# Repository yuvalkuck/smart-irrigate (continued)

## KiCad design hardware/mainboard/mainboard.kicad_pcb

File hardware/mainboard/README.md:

# Mainboard

Schematic: `mainboard.kicad_sch`. The sheet carries only the wire-colour legend. All the notes are here.

## Valve path

* The valve GPIOs come from the board manager file `components/board_manager/board_peripherals.yaml`
  (`gpio_valve_0` to `gpio_valve_7` = GPIO 1, 14, 18, 21, 22, 16, 17, 5), with `CONFIG_DEVICE_MAX_VALVES` = 8.
  All 8 relay channels are valves.
* GPIO 16/17 are UART0, so the console runs on USB Serial/JTAG.
* IO2 and IO3 (header A1, A2) are the only C6 GPIOs on the FireBeetle 2 header that are not connected.
  More valves, the 24 VAC inverter enable (P12), the
  inverter fault input (P15), the mains-detect input (P11) and the charger status inputs (P16 `STAT1`,
  P17 `STAT2`) use the I2C expander U5.
* The 3.3 V valve GPIOs go through two SN74AHCT125N quad buffers: U10 for valves 1-4 and U11 for
  valves 5-8. The buffer outputs go to J15 pins 2-9 (relay inputs IN1..IN8), which get 5 V logic. All
  `/OE` pins are tied to GND, and each chip has a 100 nF decoupling capacitor (C9, C10). The wires from the
  C6 to the buffers are named `VALVE1`-`VALVE8`.
* The 8-channel relay module is off the board. J15 (1x10, 2.54 mm) is its control header: 1 = GND,
  2-9 = IN1-IN8, 10 = +5V.
* The buffer outputs have no pull resistors. The state of the relay inputs while the C6 GPIOs float at
  reset is unknown. It depends on the input circuit of the relay module.
* The relay contacts are on the relay module, not on this board: J2 pin 1 goes to COM1..8, NO1..8 go
  to valves 1..8, and J2 pin 2 goes to the valve common.

## Power

* J1 takes +24 V DC through the 5 A fuse F3. In V1 an external 24 V DC supply feeds J1. When the battery
  add-on (`hardware/battery`) is installed, its J5 (24 V DC out) feeds J1 instead; the mainboard does not change.
* The mainboard makes its own +5V and 24 VAC from +24V. The 5S pack, its gauge and protector (BQ40Z80),
  the charger and the 24 V bus converter are on the battery add-on only.
* Optional addon: one 3.7 V 18650 cell (BT3) plugs into the on-board JST PH2.0 battery socket (J3) of A1, the
  FireBeetle 2 module. The cell and the socket are not on this board's schematic or PCB. The FireBeetle 2
  on-board charger charges the cell.
* J16 (1x8 pin header, 2.54 mm) is the link to the battery add-on J4: 1 = +5V (out, if the add-on needs it), 2 = GND,
  3 = +3V3 (out), 4 = SDA, 5 = SCL, 6 = `MAINS_OK_N` (in), 7 = `STAT1` (in), 8 = `STAT2` (in).
  `MAINS_OK_N`, `STAT1` and `STAT2` are open-drain outputs of the add-on charger, so R64, R65 and R66
  (100k to +3V3) pull them up. `MAINS_OK_N` goes to U5 P11, `STAT1` to P16 and `STAT2` to P17.
  `MAINS_OK_N` high = no mains (or no add-on).
* The battery gauge (BQ40Z80, SMBus) is on the battery add-on and is reached through J16 SDA and SCL. It reports
  each cell voltage, pack voltage and current, remaining capacity and state of charge, temperature and
  protection status. Its SMBus speed is 10 to 100 kHz in slave mode, so the shared I2C bus has to run at
  100 kHz or below when the add-on is fitted. Its slave address is not read yet.
* The ESP32-S3 (A3) runs from the switched 5 V line (DevKit 5V0 pin). Q1 (AO3401A P-FET) connects
  +5V to it, and Q2 (BSS138) drives its gate. R34 (100k) holds Q1 off when Q2 is off. The switched 5 V
  line also feeds the LCD (J6) and the HV side of the level shifter U9.
* U5 P13 controls Q2. R35 (100k) pulls it up to +3V3, so the S3 is on by default (also while P13
  floats at boot). Firmware pulls P13 low to power the S3 down.
* The battery-state LED DS12 (with R33, 470 R) is on U5 P07 (`LED_BAT`).
* The buzzer BZ1 is an active 5 V buzzer (it needs a built-in oscillator). Q3 (BSS138) switches it from
  U5 P14, R36 (2.2k) holds the gate low, and D8 (1N4148W) is the flyback diode.
* R36 and R41 are 2.2k because the U5 (TCA9555) ports power up as inputs with an internal pull-up. The
  datasheet gives 100 uA maximum for that pull-up, so the pin stays at 0.22 V or less. That is below the
  BSS138 threshold (0.5 V minimum) and below the TPS7A1601 `EN` off level (0.3 V).

## 5 V (U12, LMR51430)

* Buck from +24V, 3 A part. R37 (100k) and R38 (13.7k) set 4.98 V. L1 6.8 uH. C15 and C16 are 2 x 22 uF
  output, C12 to C14 the input capacitors. `EN` is tied to +24V.

## 24 VAC (sine inverter)

Moved from the battery board (design values unchanged, references renumbered). It runs whenever +24V is present
and firmware enables it.

* `INV_EN` comes from U5 P12. R41 (2.2k) pulls it low, so the inverter is off until firmware drives it high.
  It gates the 12 V LDO (U13 `EN`), the EG8010 `SPWMEN` and the DRV8412 `RESET_AB`. The 45 V boost enables
  itself from the 12 V rail, so it stops too.
* `INV_FAULT_N` is the DRV8412 `FAULT` pin (open collector, low = fault). It goes to U5 P15 with the R63
  (100k) pull-up to +3V3.
* 12 V (U13, TPS7A1601): R39 (1.15M) over R40 (127k) set about 12 V. C17 feed-forward, C18 input, C19 output.
  It feeds the DRV8412 `GVDD`/`VDD` (about 30 mA) and the boost enable divider. About 0.36 W at 24 V in.
* 45 V boost (U14, LM5155): R49 (107k) over R50 (2.43k) set 45.0 V, R47 (73.2k) about 298 kHz. L2 15 uH,
  Q5 switch, D9 PMEG060V100EPD diode, R44 12 m sense, R45 slope. Output C28/C29 (100 uF 63 V polymer) and
  C30 to C32 (4.7 uF 100 V). Compensation R48, C24, C25 are start values. Enable: R51/R52 divide the 12 V
  rail. Bias from +24V through R42 (0R) with C20.
* EG8010 (U15): bipolar mode, 50 Hz, soft start on, 12 MHz crystal Y1 with C33/C34. `SPWMOUT3` (left-high)
  goes to `PWM_A` through R53/R54, `SPWMOUT1` (right-high) to `PWM_B` through R55/R56 (about 3.5 V from 5 V).
* DRV8412 (U16): mode 000, only bridges A and B used. R62 (36k) sets `OC_ADJ` for about 7.4 A. R61 (1R)
  joins GND and AGND. C39 on `VREG`, C40 to C43 on `GVDD`, C46 to C49 on `PVDD`, C50 to C53 bootstrap.
* Feedback: 47k over 4.53k with 100 nF on each output line (R57/R58/C37, R59/R60/C38) into `VFB` and
  `VFB2`, about 24.1 V RMS. The EG8010 shuts down above 3.15 V peak feedback (300 ms) and below 2.75 V (3 s)
  (EG8010 datasheet, section 8.1).
* Output filter: L3 and L4 (1 mH, one in each line) and C54 (4.7 uF film) across the output. It feeds J2
  through the existing snubber/indicator R6, R30, C3, D7, DS11.

Open points of this block:

* Output common mode: each 24 VAC wire sits at about 22.5 V DC (`PVDD`/2) plus the AC, relative to GND. An
  isolating 50 Hz transformer between C54 and J2 is the proposed fix; not decided and not drawn.
* L3/L4: no part chosen; the footprint is a placeholder. D9: datasheet not read.
* The 45 V boost and the DRV8412 bridge switch near the ESP32 and the sensor inputs: keep them apart on the PCB.

## ESP32-S3 link

* IO6/IO7 are the UART1 link to A3: A3 IO17 TX goes to IO7, and IO6 goes to A3 IO18 RX. J4 (1x3 pin header,
  2.54 mm) is a logic-analyzer tap on the C6 side of the same wires: 1 = `S3_TX`, 2 = `S3_RX`, 3 = GND.
* Q4 (BSS138) isolates the C6 TX line (`S3_RX`, C6 side) from the S3 RX pin (A3 IO18) while the S3 is
  powered down. Its gate is on the switched 5 V line, so the line opens by itself when Q1 cuts the S3 supply. The drain is
  on the C6 side, so the body diode cannot feed the unpowered S3. The S3 TX line (`S3_TX`) needs no
  isolation, and R16 keeps it pulled up on the C6 side.

## RS-485 to the sensor cluster

* J5: 1 = A, 2 = B, 3 = +5V out, 4 = GND.
* The +5V out goes through F2 (MF-RHT050, 0.5 A resettable fuse). D2 (SMAJ5.0A) is on the J5 side of F2,
  and D1 (SM712) is on A and B.
* U4 is on the UART: IO9 TX goes to DI, and IO8 takes RO.
* DE and /RE are on IO15, the on-board LED, which also shows TX. R7 holds DE low at boot.
* R10 (120R) is the terminator, always connected across A and B (no jumper) because this board is the start of
  the bus. R8/R9 are the 390R bias, which sits at this end only.
* SHT41, BMP581 and the solar panel are on the sensor cluster and are read over RS-485 (J5).

## I2C

* The bus is on IO19/IO20 (header pins 28/29; pins 9/10 are the same signals).
* U5 TCA9555 is at 0x20 and U8 ADS1115 is at 0x48 (`ADDR` to GND). R17/R18 are the pull-ups. The bus also
  goes to J16 for the BQ40Z80 gauge on the battery add-on.

## Analog inputs

* U8 (ADS1115) reads all the analog inputs: AIN0 = XDB401 pressure (J9), AIN1 = wind speed (J10),
  AIN2 = board temperature U7 (MCP9700A). AIN3 is free.
* The 1.8k/3.3k dividers (R2/R1 on AIN0, R4/R3 on AIN1) scale the 0-5 V sensor outputs to 0-3.24 V.
* J8 (DS18B20): 1 = +3V3, 2 = GND, 3 = DATA. R5 (4.7k) is the 1-Wire pull-up.
* J9 (XDB401): 1 = +5V, 2 = GND, 3 = OUT.
* J10 (wind sensor): 1 = +24V, 2 = GND, 3 = OUT. The footprint has 4 terminals and terminal 4 has no net.
* Sensor cable TVS: D3 DS18B20, D4 XDB401, D5 wind OUT, D6 wind +24V. R11 limits the IO4 current.

## LCD and keys on the ESP32-S3

* J6 LCD2004 I2C: 1 = GND, 2 = VCC, 3 = SDA, 4 = SCL. On A3: IO8 is SDA and IO9 is SCL. VCC comes from the
  switched 5 V line (Q1 drain), so the LCD is off when the S3 is powered down.
* J7 (1x5 pin header, 2.54 mm) takes the 4 keys: 1 = GND, 2 = OK, 3 = UP, 4 = DOWN, 5 = BACK. A key
  connects its wire to GND. The resistor ladder is on the board: OK goes straight to the `KEYS` node,
  UP through R12 (2.2k), DOWN through R13 (5.6k), BACK through R14 (15k). `KEYS` goes to A3 IO4
  (ADC1 channel 3). R15 is a 10k pull-up to A3 3V3.

| Key | Voltage |
|---|---|
| OK | 0 V |
| UP | 0.60 V |
| DOWN | 1.18 V |
| BACK | 1.98 V |
| No key | 3.30 V |

A3 IO5-IO7 are free.

## LEDs and buttons on the ESP32-C6 side

* DS1 (main status, 5 mm) is on U5 P00 and DS2-DS7 are on P01-P06. Each LED has its cathode on the port
  and a 470 R resistor (R19-R25) to +3V3, so a low output lights it.
* J12 is the external main LED, in parallel with DS1: 1 = anode (from +3V3 through R26, 470 R),
  2 = cathode (P00).
* SW6 ("SHOW LEDs") is between U5 P10 and GND. It uses the U5 internal pull-up.
* SW1 (CONFIG) is between IO23 and GND. J13 is the external CONFIG button in parallel with it:
  1 = `CFG_SW`, 2 = GND.
* DS8, DS9 and DS10 (red) show the +24V, +5V and +3V3 rails through R27 (47k), R28 (4.7k) and R29 (2.2k).

## Test points

2.0 mm through-hole pads (`TestPoint_THTPad_D2.0mm_Drill1.0mm`), in a row along the bottom edge of the PCB.

| Ref | Net |
|---|---|
| TP1 | +24V |
| TP2 | +5V |
| TP3 | +3V3 |
| TP4 | GND |
| TP5 | `VAC24_A` (24 VAC output, line A) |
| TP6 | +12V (U13 output) |
| TP7 | `VAC24_B` (24 VAC output, line B) |

* The 24 VAC output is the voltage between `VAC24_A` and `VAC24_B`. Each line sits at about 22.5 V DC above GND
  (see the open points of the 24 VAC block), so TP5 alone does not show the 24 VAC. Both lines are also on J2.
* No test point yet for the 45 V boost output (`Net-(D9-K)`, no label in the schematic) or for `INV_EN`.

## Assembly

All Dupont parts are not assembled by the FAB, so they are marked do-not-populate (`dnp yes`) in the schematic:
the pin headers J4-J9, J12, J13, J15, J16 and the female socket rows of the two modules (A1, the ESP32-C6, and
A3, the ESP32-S3). The screw terminals J1, J2 and J10 are not marked. The PCB footprints do not have the
do-not-populate attribute yet; KiCad shows a `footprint_symbol_mismatch` warning for these 12 parts until the PCB
is updated from the schematic.

## Not drawn yet

The 24 VAC output transformer (see the open points of the 24 VAC block). The sheet is A1: the 5 V and
24 VAC blocks sit right of the original drawing and are wired to it.

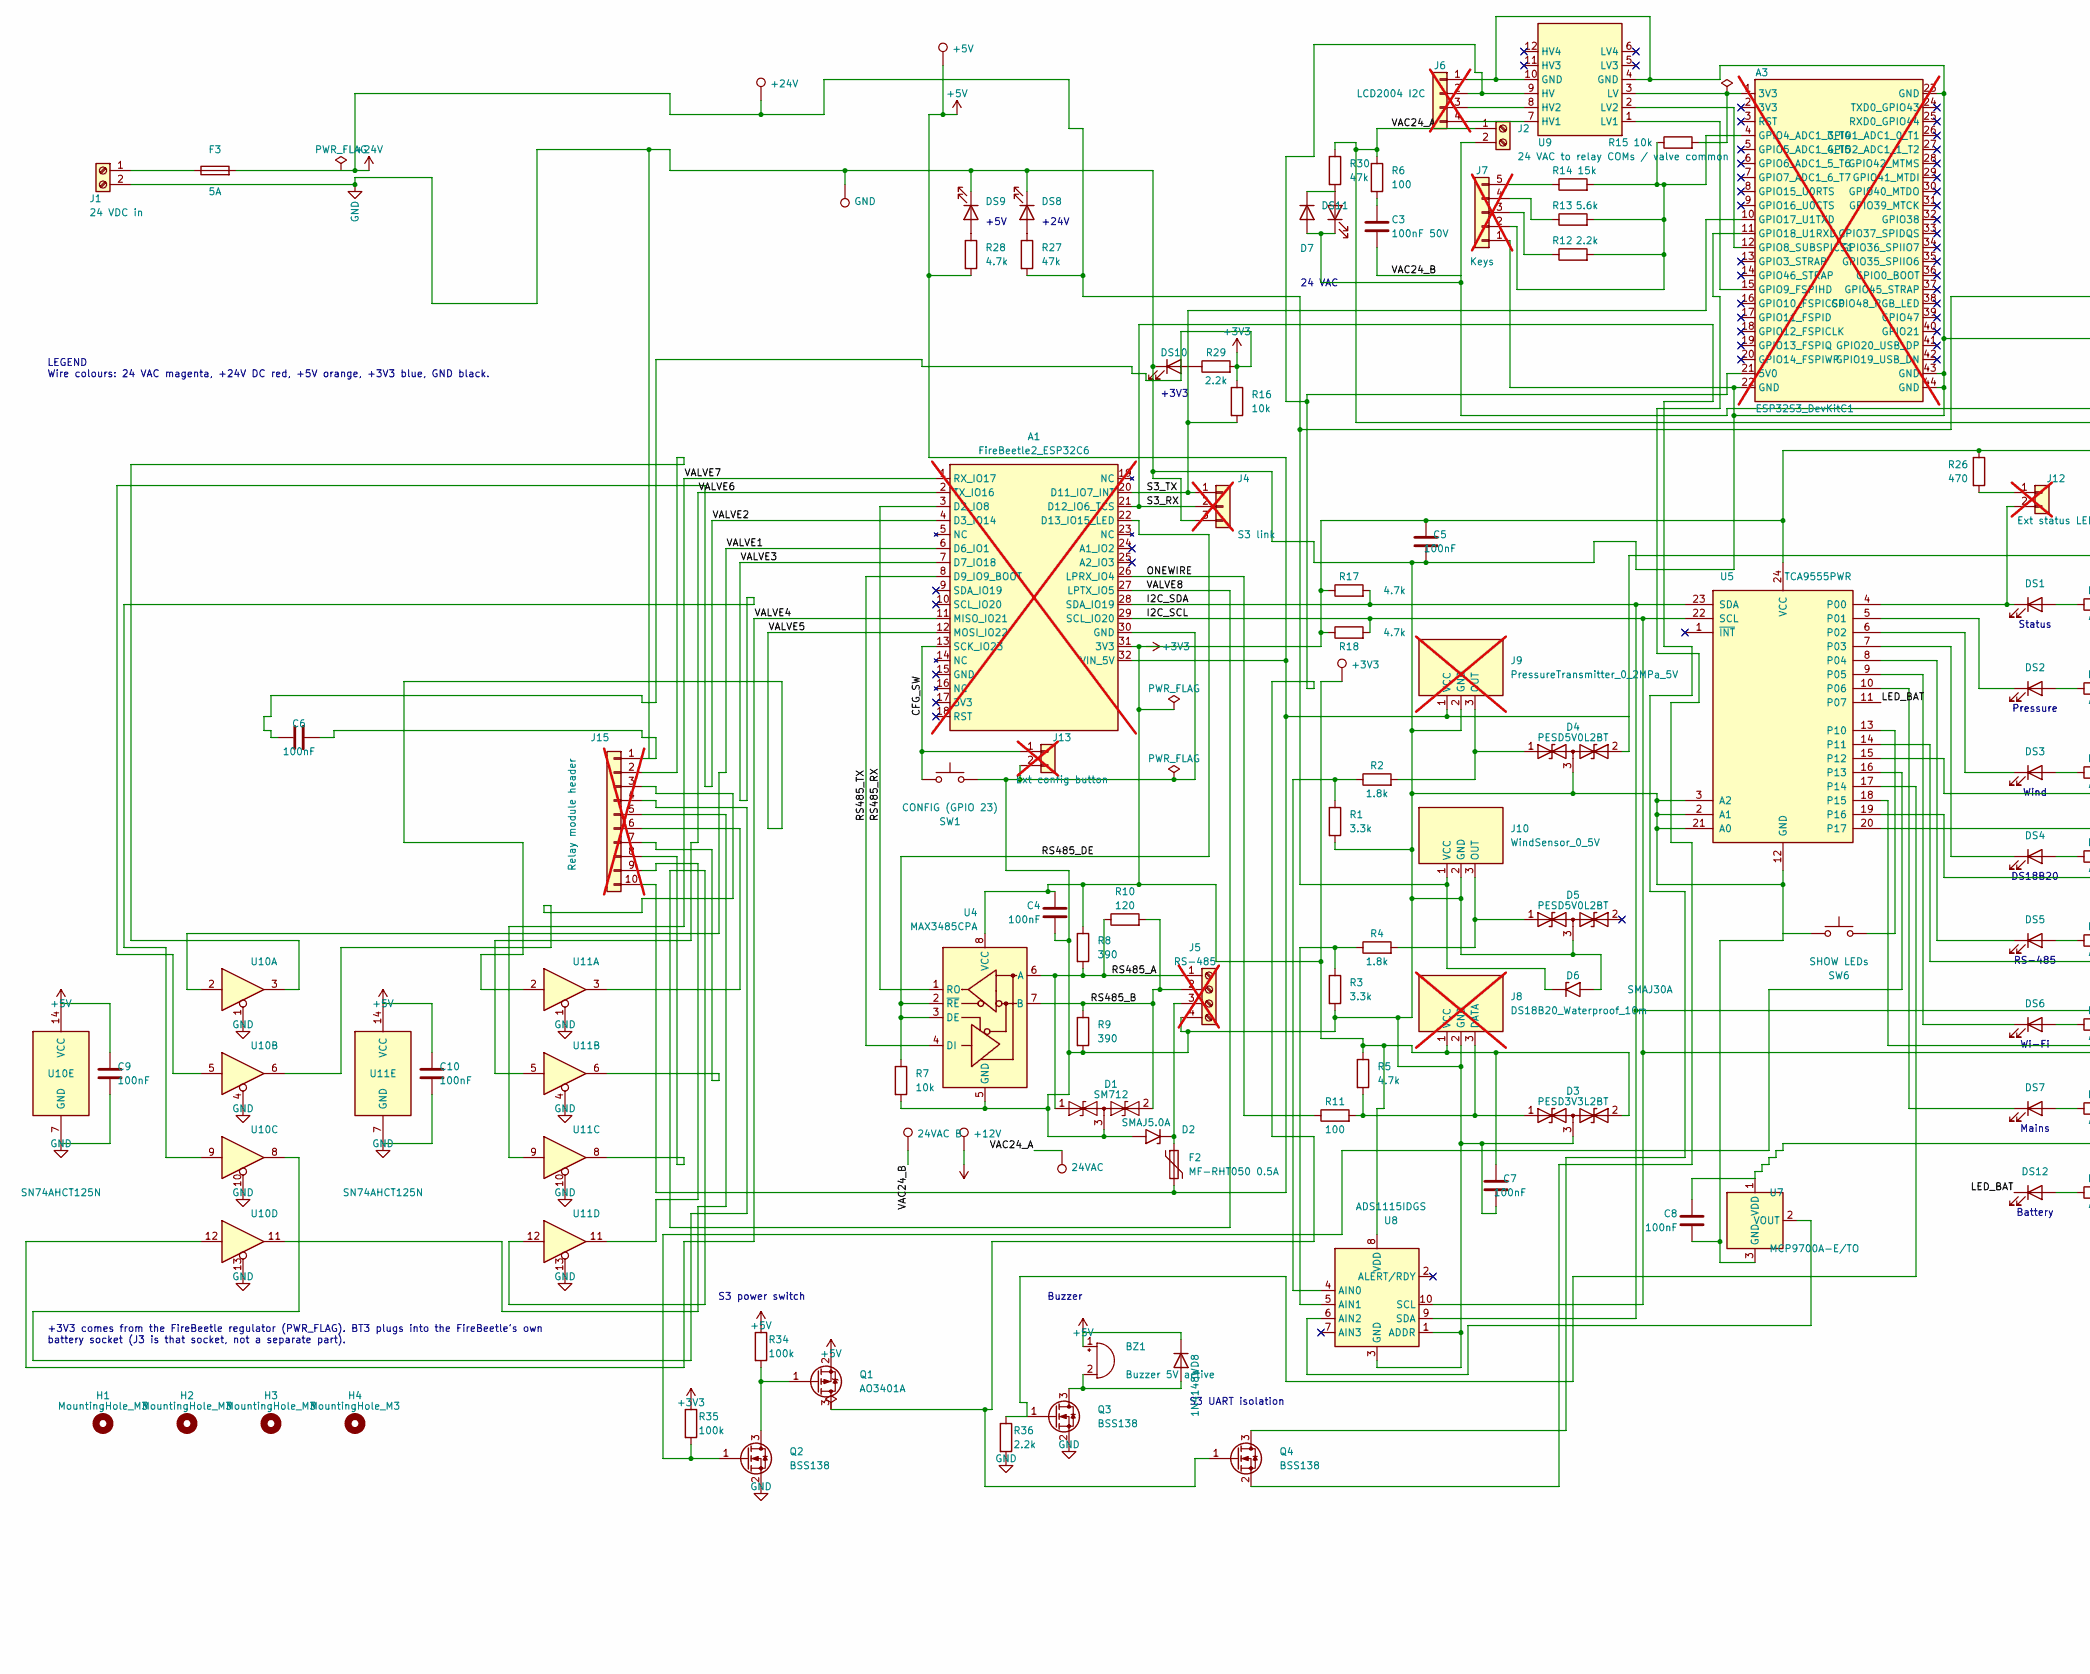
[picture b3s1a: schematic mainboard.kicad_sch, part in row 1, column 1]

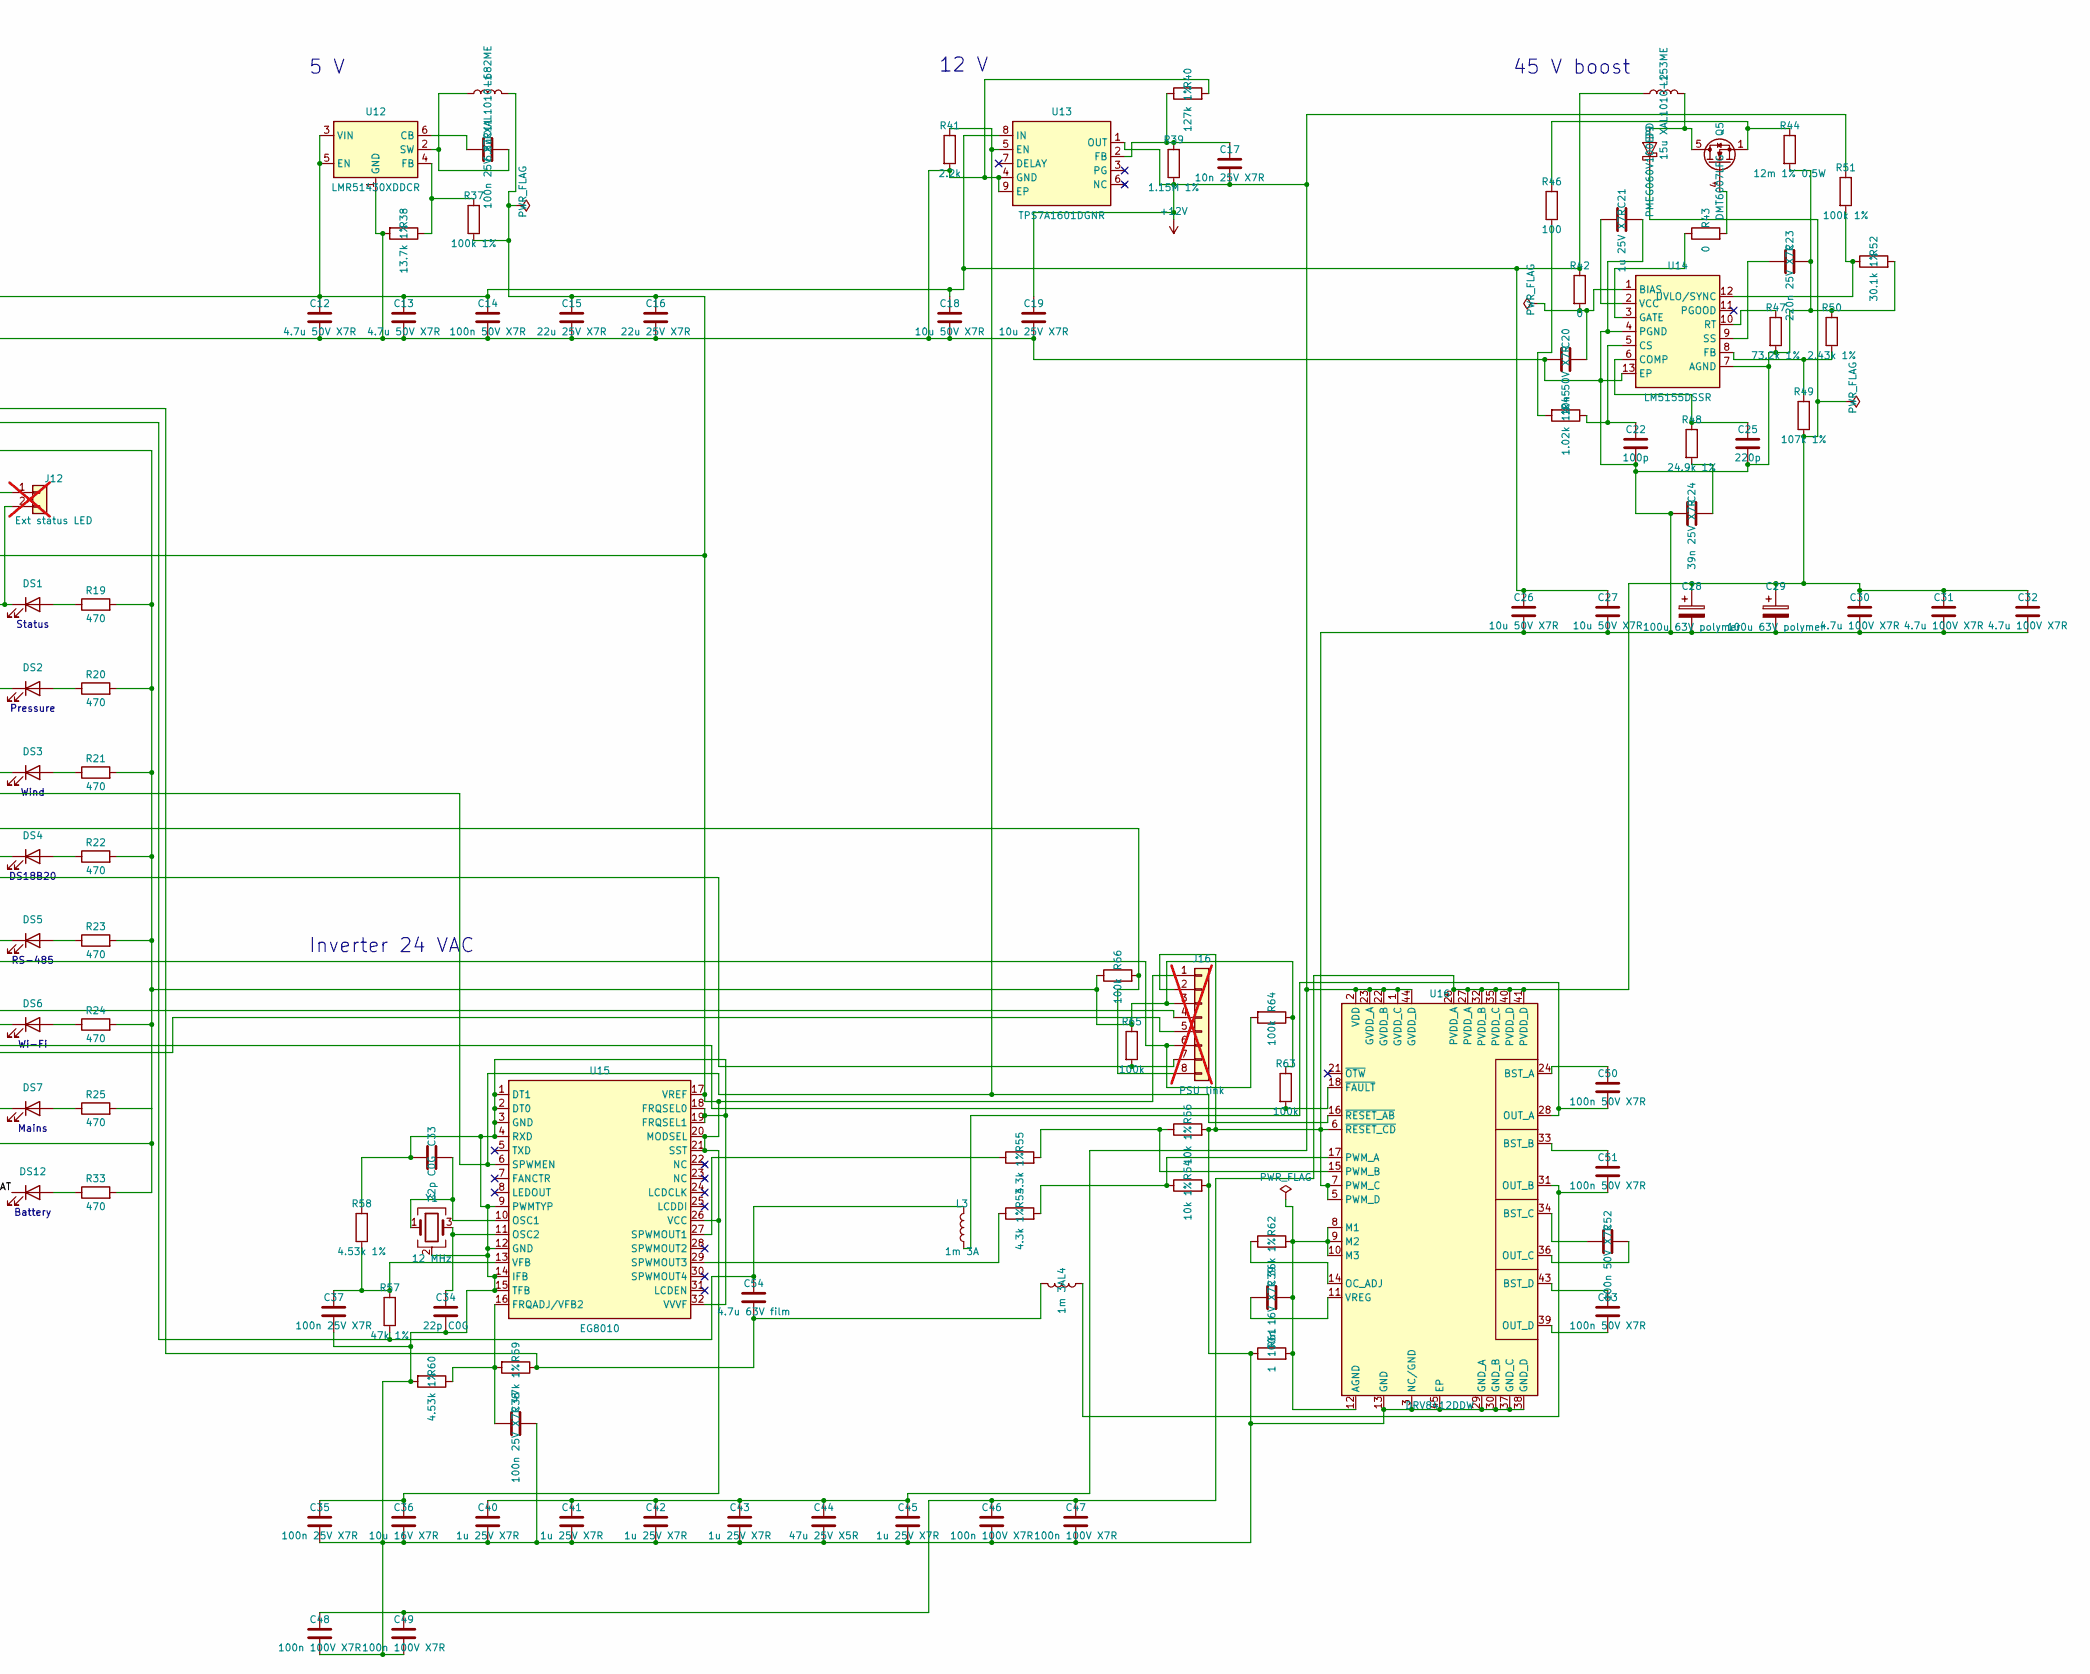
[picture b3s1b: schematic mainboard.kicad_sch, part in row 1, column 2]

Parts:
A1: FireBeetle2_ESP32C6; not fitted
A3: ESP32S3_DevKitC1; not fitted
BZ1: Buzzer 5V active; Buzzer_12x9.5RM7.6
C3: 100nF 50V; C_0805_2012Metric
C4, C5, C6, C7, C8, C9, C10: 100nF; C_0805_2012Metric
C11, C35, C37, C38: 100n 25V X7R; C_0805_2012Metric
C12, C13: 4.7u 50V X7R; C_1210_3225Metric
C14, C50, C51, C52, C53: 100n 50V X7R; C_0805_2012Metric
C15, C16: 22u 25V X7R; C_1210_3225Metric
C17: 10n 25V X7R; C_0805_2012Metric
C18, C26, C27: 10u 50V X7R; C_1210_3225Metric
C19: 10u 25V X7R; C_1210_3225Metric
C20: 10n 50V X7R; C_0805_2012Metric
C21, C40, C41, C42, C43, C45: 1u 25V X7R; C_0805_2012Metric
C22: 100p; C_0805_2012Metric
C23: 220n 25V X7R; C_0805_2012Metric
C24: 39n 25V X7R; C_0805_2012Metric
C25: 220p; C_0805_2012Metric
C28, C29: 100u 63V polymer; CP_Elec_10x10
C30, C31, C32: 4.7u 100V X7R; C_1210_3225Metric
C33, C34: 22p C0G; C_0805_2012Metric
C36: 10u 16V X7R; C_0805_2012Metric
C39: 100n 16V X7R; C_0805_2012Metric
C44: 47u 25V X5R; C_1210_3225Metric
C46, C47, C48, C49: 100n 100V X7R; C_0805_2012Metric
C54: 4.7u 63V film; C_Rect_L18.0mm_W11.0mm_P15.00mm_FKS3_FKP3
D1: SM712; SOT-23
D2: SMAJ5.0A; D_SMA
D3: PESD3V3L2BT; SOT-23
D4, D5: PESD5V0L2BT; SOT-23
D6: SMAJ30A; D_SMA
D7, D8: 1N4148W; D_SOD-123
D9: PMEG060V100EPD; Nexperia_CFP15_SOT-1289
DS1: LED 5mm green; LED_D5.0mm
DS2, DS3, DS4, DS5, DS6, DS7, DS12: LED 0805 green; LED_0805_2012Metric
DS8, DS9, DS10, DS11: LED 0805 red; LED_0805_2012Metric
F2: MF-RHT050 0.5A; Fuse_Bourns_MF-RHT050
F3: 5A; FuseHolder_5x20_ELECAPITAL_PCB_Cover
H1, H2, H3, H4: MountingHole_M3; MountingHole_3.2mm_M3
J1: 24 VDC in; TerminalBlock_MaiXu_MX126-5.0-02P_1x02_P5.00mm
J2: 24 VAC to relay COMs / valve common; TerminalBlock_MaiXu_MX126-5.0-02P_1x02_P5.00mm
J4: S3 link; PinHeader_1x03_P2.54mm_Vertical; not fitted
J5: RS-485; PinHeader_1x04_P2.54mm_Vertical; not fitted
J6: LCD2004 I2C; PinHeader_1x04_P2.54mm_Vertical; not fitted
J7: Keys; PinHeader_1x05_P2.54mm_Vertical; not fitted
J8: DS18B20_Waterproof_10m; PinHeader_1x03_P2.54mm_Vertical; not fitted
J9: PressureTransmitter_0_2MPa_5V; PinHeader_1x03_P2.54mm_Vertical; not fitted
J10: WindSensor_0_5V; TerminalBlock_MaiXu_MX126-5.0-04P_1x04_P5.00mm
J12: Ext status LED; PinHeader_1x02_P2.54mm_Vertical; not fitted
J13: Ext config button; PinHeader_1x02_P2.54mm_Vertical; not fitted
J15: Relay module header; PinHeader_1x10_P2.54mm_Vertical; not fitted
J16: PSU link; PinHeader_1x08_P2.54mm_Vertical; not fitted
L1: 6.8u XAL1010-682ME; XAL1010
L2: 15u XAL1010-153ME; XAL1010
L3, L4: 1m 3A; L_Toroid_Vertical_L21.6mm_W11.4mm_P7.62mm_Pulse_KM-3
Q1: AO3401A; SOT-23
Q2, Q3, Q4: BSS138; SOT-23
Q5: DMT6007LFG; Diodes_PowerDI3333-8
R1, R3: 3.3k; R_0805_2012Metric
R2, R4: 1.8k; R_0805_2012Metric
R5, R17, R18, R28: 4.7k; R_0805_2012Metric
R6, R11, R46: 100; R_0805_2012Metric
R7, R15, R16: 10k; R_0805_2012Metric
R8, R9: 390; R_0805_2012Metric
R10: 120; R_0805_2012Metric
R12, R29, R36, R41: 2.2k; R_0805_2012Metric
R13: 5.6k; R_0805_2012Metric
R14: 15k; R_0805_2012Metric
R19, R20, R21, R22, R23, R24, R25, R26, R33: 470; R_0805_2012Metric
R27, R30: 47k; R_0805_2012Metric
R34, R35, R63, R64, R65, R66: 100k; R_0805_2012Metric
R37, R51: 100k 1%; R_0805_2012Metric
R38: 13.7k 1%; R_0805_2012Metric
R39: 1.15M 1%; R_0805_2012Metric
R40: 127k 1%; R_0805_2012Metric
R42, R43: 0; R_0805_2012Metric
R44: 12m 1% 0.5W; R_1206_3216Metric
R45: 1.02k 1%; R_0805_2012Metric
R47: 73.2k 1%; R_0805_2012Metric
R48: 24.9k 1%; R_0805_2012Metric
R49: 107k 1%; R_0805_2012Metric
R50: 2.43k 1%; R_0805_2012Metric
R52: 30.1k 1%; R_0805_2012Metric
R53, R55: 4.3k 1%; R_0805_2012Metric
R54, R56: 10k 1%; R_0805_2012Metric
R57, R59: 47k 1%; R_0805_2012Metric
R58, R60: 4.53k 1%; R_0805_2012Metric
R61: 1; R_0805_2012Metric
R62: 36k 1%; R_0805_2012Metric
SW1: CONFIG (GPIO 23); SW_Tactile_6x6x5_2pin
SW6: SHOW LEDs; SW_Tactile_6x6x5_2pin
TP1: +24V; TestPoint_THTPad_D2.0mm_Drill1.0mm
TP2: +5V; TestPoint_THTPad_D2.0mm_Drill1.0mm
TP3: +3V3; TestPoint_THTPad_D2.0mm_Drill1.0mm
TP4: GND; TestPoint_THTPad_D2.0mm_Drill1.0mm
TP5: 24VAC; TestPoint_THTPad_D2.0mm_Drill1.0mm
TP6: +12V; TestPoint_THTPad_D2.0mm_Drill1.0mm
TP7: 24VAC B; TestPoint_THTPad_D2.0mm_Drill1.0mm
U4: MAX3485CPA; DIP-8_W7.62mm
U5: TCA9555PWR; TSSOP-24_4.4x7.8mm_P0.65mm
U7: MCP9700A-E/TO; TO-92_Inline
U8: ADS1115IDGS; TSSOP-10_3x3mm_P0.5mm
U9: LogicLevelConverter_BSS138_4ch
U10, U11: SN74AHCT125N; DIP-14_W7.62mm
U12: LMR51430XDDCR; SOT-23-6
U13: TPS7A1601DGNR; HVSSOP-8-1EP_3x3mm_P0.65mm_EP1.57x1.89mm
U14: LM5155DSSR; WSON-12-1EP_3x2mm_P0.5mm_EP1x2.65
U15: EG8010; LQFP-32_7x7mm_P0.8mm
U16: DRV8412DDW; HTSSOP-44-1EP_6.1x14mm_P0.635mm_EP5.2x14mm_Mask4.31x8.26mm_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
Y1: 12 MHz; Crystal_SMD_3225-4Pin_3.2x2.5mm

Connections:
+3V3: A1.31 (3V3), C4.1, C5.1, C6.1, C7.1, C8.1, D3.2 (A2), J8.1 (VCC), J16.3, R5.1, R8.1, R16.1, R17.1, R18.1, R19.2, R20.2, R21.2, R22.2, R23.2, R24.2, R25.2, R26.1, R29.2, R33.2, R35.1, R63.1, R64.1, R65.1, R66.1, TP3.1 (1_1), U4.8 (VCC), U5.24 (VCC), U7.1 (VDD), U8.8 (VDD)
+5V: A1.32 (VIN_5V), BZ1.1 (+), C9.1, C10.1, C15.1, C16.1, C35.1, C36.1, D4.2 (A2), D8.1 (K), F2.2, J9.1 (VCC), J15.10, J16.1, L1.2, Q1.2 (S), R28.2, R34.1, R37.1, TP2.1 (1_1), U10.14 (VCC), U11.14 (VCC), U15.17 (VREF), U15.20 (MODSEL), U15.21 (SST), U15.26 (VCC)
+12V: C17.1, C19.1, C40.1, C41.1, C42.1, C43.1, C44.1, C45.1, R39.1, R51.1, TP6.1 (1_1), U13.1 (OUT), U16.1 (GVDD_C), U16.2 (VDD), U16.22 (GVDD_B), U16.23 (GVDD_A), U16.44 (GVDD_D)
+24V: C12.1, C13.1, C14.1, C18.1, C26.1, C27.1, D6.1 (A1), F3.2, J10.1 (VCC), L2.1, R27.2, R42.1, TP1.1 (1_1), U12.3 (VIN), U12.5 (EN), U13.8 (IN)
/CFG_SW: A1.13 (SCK_IO23), J13.1, SW1.1
/I2C_SCL: A1.29 (SCL_IO20), J16.5, R18.2, U5.22 (SCL), U8.10 (SCL)
/I2C_SDA: A1.28 (SDA_IO19), J16.4, R17.2, U5.23 (SDA), U8.9 (SDA)
/LED_BAT: DS12.1 (K), U5.11 (P07)
/ONEWIRE: A1.26 (LPRX_IO4), R11.1
/RS485_A: D1.1 (A1), J5.1, R8.2, R10.1, U4.6 (A)
/RS485_B: D1.2 (A2), J5.2, R9.1, R10.2, U4.7 (B)
/RS485_DE: A1.22 (D13_IO15_LED), R7.1, U4.2 (~RE), U4.3 (DE)
/RS485_RX: A1.3 (D2_IO8), U4.1 (RO)
/RS485_TX: A1.8 (D9_IO9_BOOT), U4.4 (DI)
/S3_RX: A1.21 (D12_IO6_TCS), J4.2, Q4.3 (D)
/S3_TX: A1.20 (D11_IO7_INT), A3.10 (GPIO17_U1TXD), J4.1, R16.2
/VAC24_A: C54.1, J2.1, L3.2, R6.1, R30.1, R57.1, TP5.1 (1_1)
/VAC24_B: C3.2, C54.2, D7.2 (A), DS11.1 (K), J2.2, L4.2, R59.1, TP7.1 (1_1)
/VALVE1: A1.6 (D6_IO1), U10.2
/VALVE2: A1.4 (D3_IO14), U10.5
/VALVE3: A1.7 (D7_IO18), U10.9
/VALVE4: A1.11 (MISO_IO21), U10.12
/VALVE5: A1.12 (MOSI_IO22), U11.2
/VALVE6: A1.2 (TX_IO16), U11.5
/VALVE7: A1.1 (RX_IO17), U11.9
/VALVE8: A1.27 (LPTX_IO5), U11.12
GND: A1.30 (GND), A3.22 (GND), A3.23 (GND), A3.43 (GND), A3.44 (GND), C4.2, C5.2, C6.2, C7.2, C8.2, C9.2, C10.2, C12.2, C13.2, C14.2, C15.2, C16.2, C18.2, C19.2, C20.2, C21.2, C22.2, C23.2, C24.2, C25.2, C26.2, C27.2, C28.2, C29.2, C30.2, C31.2, C32.2, C33.2, C34.2, C35.2, C36.2, C37.2, C38.2, C40.2, C41.2, C42.2, C43.2, C44.2, C45.2, C46.2, C47.2, C48.2, C49.2, D1.3 (common), D2.2 (A2), D3.3 (common), D4.3 (common), D5.3 (common), D6.2 (A2), DS8.1 (K), DS9.1 (K), DS10.1 (K), J1.2, J4.3, J5.4, J6.1, J7.1, J8.2 (GND), J9.2 (GND), J10.2 (GND), J13.2, J15.1, J16.2, Q2.2 (S), Q3.2 (S), R1.2, R3.2, R7.2, R9.2, R36.2, R38.2, R40.2, R41.2, R44.2, R47.2, R50.2, R52.2, R54.2, R56.2, R58.2, R60.2, R61.1, SW1.2, SW6.1, TP4.1 (1_1), U4.5 (GND), U5.2 (A1), U5.3 (A2), U5.12 (GND), U5.21 (A0), U7.3 (GND), U8.1 (ADDR), U8.3 (GND), U9.4 (GND), U9.10 (GND), U10.1, U10.4, U10.7 (GND), U10.10, U10.13, U11.1, U11.4, U11.7 (GND), U11.10, U11.13, U12.1 (GND), U13.4 (GND), U13.9 (EP), U14.4 (PGND), U14.7 (AGND), U14.13 (EP), U15.1 (DT1), U15.2 (DT0), U15.3 (GND), U15.4 (RXD), U15.9 (PWMTYP), U15.12 (GND), U15.14 (IFB), U15.15 (TFB), U15.18 (FRQSEL0), U15.19 (FRQSEL1), U15.32 (VVVF), U16.3 (NC/GND), U16.4 (NC/GND), U16.5 (PWM_D), U16.6 (~RESET_CD), U16.7 (PWM_C), U16.13 (GND), U16.19 (NC/GND), U16.20 (NC/GND), U16.25 (NC/GND), U16.29 (GND_A), U16.30 (GND_B), U16.37 (GND_C), U16.38 (GND_D), U16.42 (NC/GND), U16.45 (EP), Y1.2 (G), Y1.4 (G)
unnamed: A3.21 (5V0), J6.2, Q1.3 (D), Q4.1 (G), U9.9 (HV)
unnamed: A3.4 (GPIO4_ADC1_3_T4), J7.2, R12.2, R13.2, R14.2, R15.1
unnamed: A3.12 (GPIO8_SUBSPICS1), U9.2 (LV2)
unnamed: A3.15 (GPIO9_FSPIHD), U9.1 (LV1)
unnamed: A3.11 (GPIO18_U1RXD), Q4.2 (S)
unnamed: BZ1.2 (-), D8.2 (A), Q3.3 (D)
unnamed: C3.1, R6.2
unnamed: C24.1, R48.2
unnamed: D2.1 (A1), F2.1, J5.3
unnamed: D3.1 (A1), J8.3 (DATA), R5.2, R11.2
unnamed: D4.1 (A1), J9.3 (OUT), R2.2
unnamed: D5.1 (A1), J10.3 (OUT), R4.2
unnamed: D7.1 (K), DS11.2 (A), R30.2
unnamed: C28.1, C29.1, C30.1, C31.1, C32.1, C46.1, C47.1, C48.1, C49.1, D9.3 (K), R49.1, U16.26 (PVDD_A), U16.27 (PVDD_A), U16.32 (PVDD_B), U16.35 (PVDD_C), U16.40 (PVDD_D), U16.41 (PVDD_D)
unnamed: DS1.2 (A), R19.1
unnamed: DS1.1 (K), J12.2, U5.4 (P00)
unnamed: DS2.2 (A), R20.1
unnamed: DS2.1 (K), U5.5 (P01)
unnamed: DS3.2 (A), R21.1
unnamed: DS3.1 (K), U5.6 (P02)
unnamed: DS4.2 (A), R22.1
unnamed: DS4.1 (K), U5.7 (P03)
unnamed: DS5.2 (A), R23.1
unnamed: DS5.1 (K), U5.8 (P04)
unnamed: DS6.2 (A), R24.1
unnamed: DS6.1 (K), U5.9 (P05)
unnamed: DS7.2 (A), R25.1
unnamed: DS7.1 (K), U5.10 (P06)
unnamed: DS8.2 (A), R27.1
unnamed: DS9.2 (A), R28.1
unnamed: DS10.2 (A), R29.1
unnamed: DS12.2 (A), R33.1
unnamed: F3.1, J1.1
unnamed: J6.3, U9.8 (HV2)
unnamed: J6.4, U9.7 (HV1)
unnamed: J7.3, R12.1
unnamed: J7.4, R13.1
unnamed: J7.5, R14.1
unnamed: J12.1, R26.2
unnamed: J15.2, U10.3
unnamed: J15.3, U10.6
unnamed: J15.4, U10.8
unnamed: J15.5, U10.11
unnamed: J15.6, U11.3
unnamed: J15.7, U11.6
unnamed: J15.8, U11.8
unnamed: J15.9, U11.11
unnamed: J16.6, R64.2, U5.14 (P11)
unnamed: J16.7, R65.2, U5.19 (P16)
unnamed: J16.8, R66.2, U5.20 (P17)
unnamed: Q1.1 (G), Q2.3 (D), R34.2
unnamed: Q2.1 (G), R35.2, U5.16 (P13)
unnamed: Q3.1 (G), R36.1, U5.17 (P14)
unnamed: D9.1 (A), D9.2 (A), L2.2, Q5.5 (D)
unnamed: Q5.4 (G), R43.2
unnamed: Q5.1 (S), Q5.2 (S), Q5.3 (S), R44.1, R46.2
unnamed: R45.2, R46.1
unnamed: SW6.2, U5.13 (P10)
unnamed: U7.2 (VOUT), U8.6 (AIN2)
unnamed: R1.1, R2.1, U8.4 (AIN0)
unnamed: R3.1, R4.1, U8.5 (AIN1)
unnamed: A3.1 (3V3), R15.2, U9.3 (LV)
unnamed: C11.1, U12.6 (CB)
unnamed: R37.2, R38.1, U12.4 (FB)
unnamed: C11.2, L1.1, U12.2 (SW)
unnamed: R41.1, U5.15 (P12), U13.5 (EN), U15.6 (SPWMEN), U16.16 (~RESET_AB)
unnamed: C17.2, R39.2, R40.1, U13.2 (FB)
unnamed: C20.1, R42.2, U14.1 (BIAS)
unnamed: C25.1, R48.1, U14.6 (COMP)
unnamed: C22.1, R45.1, U14.5 (CS)
unnamed: R49.2, R50.1, U14.8 (FB)
unnamed: R43.1, U14.3 (GATE)
unnamed: R47.1, U14.10 (RT)
unnamed: C23.1, U14.9 (SS)
unnamed: R51.2, R52.1, U14.12 (UVLO/SYNC)
unnamed: C21.1, U14.2 (VCC)
unnamed: C38.1, R59.2, R60.1, U15.16 (FRQADJ/VFB2)
unnamed: C33.1, U15.10 (OSC1), Y1.1
unnamed: C34.1, U15.11 (OSC2), Y1.3
unnamed: R55.1, U15.27 (SPWMOUT1)
unnamed: R53.1, U15.29 (SPWMOUT3)
unnamed: C37.1, R57.2, R58.1, U15.13 (VFB)
unnamed: C39.2, R61.2, R62.2, U16.8 (M1), U16.9 (M2), U16.10 (M3), U16.12 (AGND)
unnamed: C50.1, U16.24 (BST_A)
unnamed: C51.1, U16.33 (BST_B)
unnamed: C52.1, U16.34 (BST_C)
unnamed: C53.1, U16.43 (BST_D)
unnamed: R62.1, U16.14 (OC_ADJ)
unnamed: C50.2, L3.1, U16.28 (OUT_A)
unnamed: C51.2, L4.1, U16.31 (OUT_B)
unnamed: C52.2, U16.36 (OUT_C)
unnamed: C53.2, U16.39 (OUT_D)
unnamed: R53.2, R54.1, U16.17 (PWM_A)
unnamed: R55.2, R56.1, U16.15 (PWM_B)
unnamed: C39.1, U16.11 (VREG)
unnamed: R63.2, U5.18 (P15), U16.18 (~FAULT)

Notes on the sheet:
+5V
+24V
Mains
S3 UART isolation
12 V
5 V
Wind
45 V boost
+3V3 comes from the FireBeetle regulator (PWR_FLAG). BT3 plugs into the FireBeetle's own battery socket (J3 is that socket, not a separate part).
Battery
S3 power switch
+3V3
Inverter 24 VAC
24 VAC
DS18B20
Buzzer
LEGEND Wire colours: 24 VAC magenta, +24V DC red, +5V orange, +3V3 blue, GND black.
Pressure
RS-485
Wi-Fi
Status

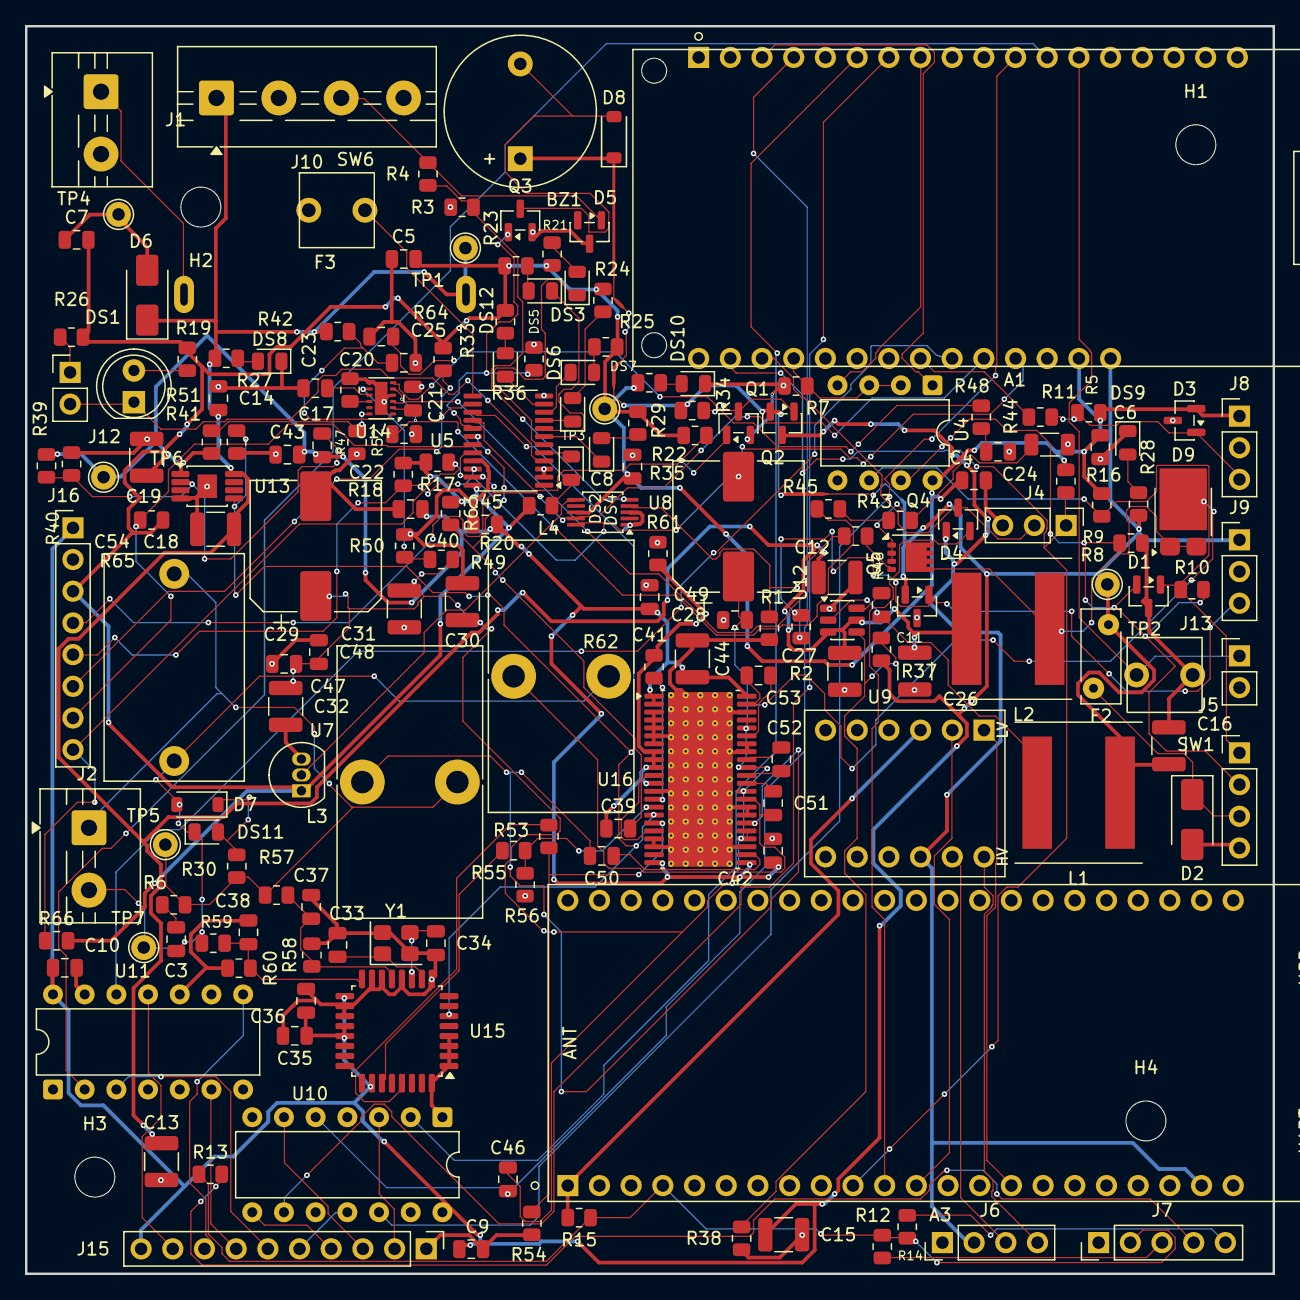
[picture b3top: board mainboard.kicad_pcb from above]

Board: 2 copper layers, 100.0 x 100.0 mm, 190 parts (0 on the bottom side), 123 nets.

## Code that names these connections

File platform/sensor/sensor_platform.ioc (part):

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Mcu.Name=STM32C011F(4-6)Px
Mcu.Package=TSSOP20
Mcu.UserName=STM32C011F6Px
PA0.GPIOParameters=GPIO_Label
PA0.GPIO_Label=SOLAR_ADC
PA0.Mode=IN0
PA0.Signal=ADC1_IN0
PA1.GPIOParameters=GPIO_Label
PA1.GPIO_Label=RS485_DE
PA1.Mode=Hardware Flow Control (RS485)
PA1.Signal=USART2_DE
PA13.Mode=Serial_Wire
PA13.Signal=DEBUG_SWDIO
PA14-BOOT0.Mode=Serial_Wire
PA14-BOOT0.Signal=DEBUG_SWCLK
PA2.GPIOParameters=GPIO_Label
PA2.GPIO_Label=RS485_TX
PA2.Mode=Asynchronous
PA2.Signal=USART2_TX
PA3.GPIOParameters=GPIO_Label
PA3.GPIO_Label=RS485_RX
PA3.Mode=Asynchronous
PA3.Signal=USART2_RX
PA4.GPIOParameters=GPIO_Label
PA4.GPIO_Label=WIND_ADC
PA4.Mode=IN4
PA4.Signal=ADC1_IN4
PA5.GPIOParameters=GPIO_PuPd,GPIO_Label
PA5.GPIO_Label=WIND_FITTED
PA5.GPIO_PuPd=GPIO_PULLUP
PA5.Signal=GPIO_Input
PB6.GPIOParameters=GPIO_Label
PB6.GPIO_Label=I2C_SCL
PB6.Mode=I2C
PB6.Signal=I2C1_SCL
PB7.GPIOParameters=GPIO_Label
PB7.GPIO_Label=I2C_SDA
PB7.Mode=I2C
PB7.Signal=I2C1_SDA
RCC.HSE_VALUE=8000000
RCC.SYSCLKFreq_VALUE=12000000
board=custom
